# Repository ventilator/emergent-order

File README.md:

# /dev/emergent_order

An experiment in chaos and structure, presented at 39c3 (39th Chaos Communication Congress).

A 1×1×1m LED cube art installation filled with 1200 individually addressable WS2812B LEDs, creating a volumetric 3D display.

## Overview

This repository contains most materials involved in creating the LED cube installation: software, firmware, animations, 3D mechanical parts, PCB designs, calibration tools, and documentation. The aim is to document the complete structure of the cube and make relevant tools and designs available to others who want to build their own version, learn from the project, create derivative works, or apply these concepts in entirely new ways.

## Project Structure

This repository contains the following subdirectories:

**Note:** Some directories mentioned below may not yet be available in the repository. We are actively uploading the remaining materials and expect to have everything published within the next few days.

### Hardware & Electronics

- **`controller_pcb/`** - KiCad project for a high-performance 8-channel WS2812 controller based on the Raspberry Pi Pico. Features include USB streaming mode, standalone operation with built-in test patterns, SD card playback, comprehensive monitoring (voltage, current, temperature), and per-channel smart fuse protection (3.7A). Supports up to 200 LEDs per channel at 60Hz. See [controller_pcb/README.md](controller_pcb/README.md) for complete specifications.

- **`pico_firmware/`** - C firmware for the Raspberry Pi Pico that drives 8 independent WS2812B channels via PIO hardware. Features gamma correction, automatic current limiting, hardware monitoring (temperature, current, voltage), channel fault detection, and built-in test patterns including a ternary-encoded calibration pattern for camera-based position recovery. See [pico_firmware/README.md](pico_firmware/README.md) for protocol specification and development setup.

- **`mechanical/`** - 3D printable parts (base, corners, combs, controller mounts) and carbon fiber tube specifications for building the physical cube structure. See [mechanical/README.md](mechanical/README.md) for details.

### Software & Control

- **`showrunner/`** - Node.js service that plays LED animations on the cube, streaming frames at 30-60 FPS over serial to the Pico firmware. Supports hot-swappable animations and WebSocket interface for live streaming. See [showrunner/README.md](showrunner/README.md) for details.

- **`animations/`** - JavaScript animation scripts that generate LED patterns using 3D math (SDF primitives, planes, spheres, fire effects, etc.). See [animations/README.md](animations/README.md) for examples and animation format.

- **`animation_designer/`** - Web-based tool for designing and previewing animations before deploying them to the cube. See [animation_designer/README.md](animation_designer/README.md) for usage instructions.

### Calibration & Utilities

- **`calibration/`** - Tools for recovering 3D LED positions from video captures of the cube. Includes video frame extraction, LED detection with ternary color-coded identification, and multi-camera 3D triangulation with bundle adjustment. Features both Python CLI tools and a web-based detector with real-time visualization. See [calibration/README.md](calibration/README.md) for complete workflow and encoding scheme documentation.

- **`ws2serial/`** - Python utility for testing and interfacing with WS2812 LED strips over USB serial during development. Provides a WebSocket-to-serial adapter allowing the animation designer web tool to stream pixel data over the network to the Pico controller. See [ws2serial/README.md](ws2serial/README.md) for details.

- **`testdevice/`** - MicroPython code for ESP32-C3 to quickly test single LED strings during installation and teardown. See [testdevice/README.md](testdevice/README.md) for details.

### Prototypes

- **`minikube/`** - Smaller ~20×20×20cm prototype cube with MicroPython firmware and mechanical designs for ESP32-C3. See [minikube/README.md](minikube/README.md) for details.

## Technical Specifications

- **Physical size:** 1×1×1 meter cube
- **LEDs:** 1200 individually addressable WS2812B LEDs
- **Structure:** Carbon fiber tubes (20×18mm) with 3D printed corner connectors
- **Controller:** Raspberry Pi Pico-based 8-channel controller (can be driven by Raspberry Pi 3 or run standalone)
- **Power:** Custom 4-layer PCB with 8-channel power distribution, smart fuse protection (3.7A per channel), and comprehensive monitoring
- **Software:** Node.js showrunner + JavaScript animation framework (USB streaming), or standalone test patterns
- **Communication:** USB serial (Pi 3 → Pico), PIO-based WS2812B output, WebSocket interface for live animation streaming

## Development Approach

Most of the code in this project was synthesized ("vibe coded") using various Anthropic Claude models. The goal was to rapidly prototype and get something working, so the code may not be well understood in all places or may contain bugs. However, key decisions about architecture, algorithms and artistic content were provided by humans, just not manually implemented line-by-line.

## License

See the license files in individual directories or license text in source files.

In general:
- **Code/Software:** MIT License
- **3D Models:** CC-BY 4.0
- **PCB Designs:** CERN-OHL-W (CERN Open Hardware License - Weakly Reciprocal)

## Contributing

This project was created for 39c3. Feel free to fork, modify, and create your own versions. If you build something based on this work, we'd love to hear about it!

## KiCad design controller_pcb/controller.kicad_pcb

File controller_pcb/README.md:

# 8-Channel WS2812 Controller

High-performance WS2812 LED controller based on the Raspberry Pi Pico, designed for driving large LED installations with up to 8 independent channels.

## Features

- **8 independent WS2812 channels** - Drive up to 200 LEDs per channel @ 60Hz
- **Multiple operation modes:**
  - USB streaming mode (real-time control from computer)
  - Standalone mode (run animations directly on Pico)
  - SD card playback mode (hardware ready, firmware not yet implemented)
- **Built-in test patterns** for calibration and diagnostics
- **Comprehensive monitoring** - voltage, current, and temperature sensing
- **Advanced protection** - smart fuses, PTC, and TVS diodes

## Hardware Specifications

### PCB Design
- **4-layer PCB**
- **Raspberry Pi Pico** microcontroller (direct solder or via header)
- Compact form factor

### LED Output Channels
- **8 independent channels** driven via PIO state machines
- **3.3V to 5V level shifters** for reliable WS2812 communication
- **Smart fuse protection** (TPS259251) set to 3.7A per channel
- **TVS diodes** on all data lines for protection

### Power System
- **5V input** via XT60 connector
- **Input PTC** for overcurrent protection
- **5V auxiliary output** for powering additional devices (fans, Raspberry Pi, etc.)
- **INA226 current/voltage monitor** for real-time power consumption tracking

### Sensing and Monitoring
- **Input power monitoring** via INA226 (voltage and current)
- **2× NTC temperature sensors** for thermal monitoring
- **Per-channel voltage sensing** via 8:1 analog multiplexer
- **Trip detection** - automatic fault detection when channels go offline

### User Interface
- **2 buttons** for pattern selection and reset
- **2 status LEDs** (activity and fault indicators)
- **I2C OLED display header** for local status display (optional)

### Storage
- **SD card slot** for storing animations and configuration files
- **Note:** SD card support is not currently implemented in the firmware, but it was verified that the slot is correctly wired and the Pico can access data on an SD card

## Implementation & Assembly Notes

### Capacitors
- The layout contains space for through-hole capacitors on the input rail and on each output rail
- These were not fitted on the controller that ran the installation and can be considered optional

### Channel Output Connectors
- The pin headers on the channel outputs do fit into JST-SM plugs commonly used with LED strings
- However, the spacing of the pin headers is too tight for two JST-SM plugs next to each other
- There is no mechanical interlocking, and if you pass any decent current (over 1A) these connections will get quite warm, especially if not well inserted
- **Recommendation:** For the controller used in the installation, we soldered pigtails with JST-SM sockets directly to the controller PCB for more reliable connections

### Pico Mounting
- The Pi Pico was mounted with a socket to allow easier exchange in case of failure
- This is recommended over direct soldering for serviceability

## Firmware

See `../pico_firmware/` for the Raspberry Pi Pico firmware source code.

## License

Hardware design licensed under **CERN-OHL-W** (CERN Open Hardware License - Weakly Reciprocal)

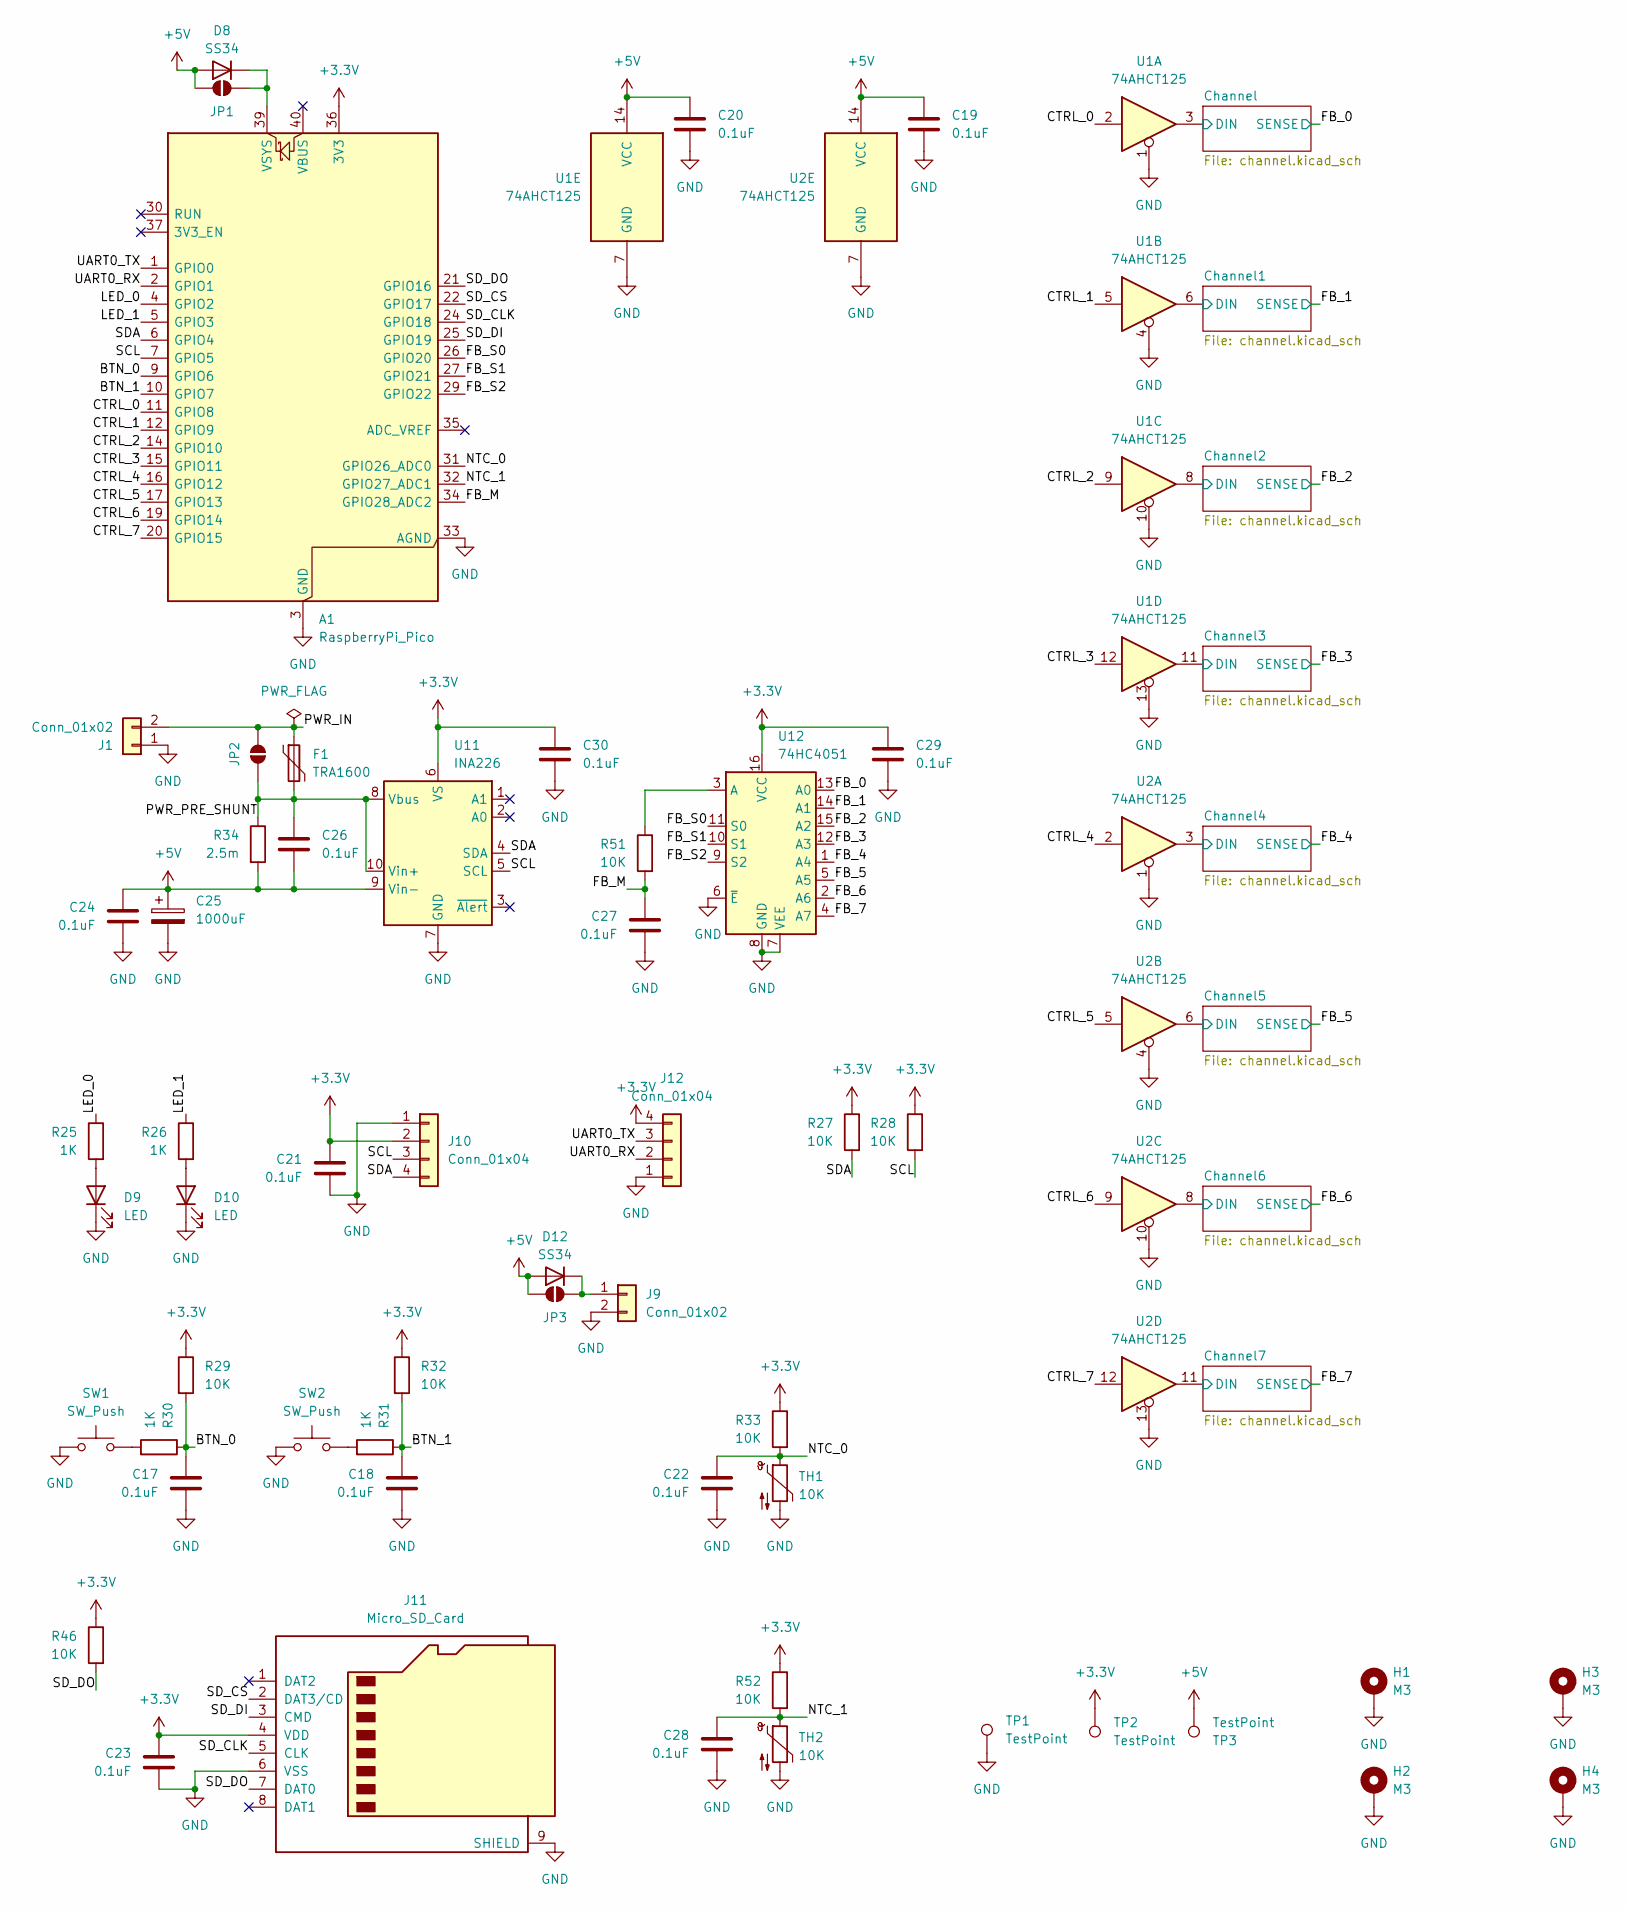
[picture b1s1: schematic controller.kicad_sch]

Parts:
A1: RaspberryPi_Pico; RaspberryPi_Pico_Common_Unspecified
C17, C18, C19, C20, C21, C22, C23, C24, C26, C27, C28, C29, C30: 0.1uF; C_0603_1608Metric
C25: 1000uF; C_Radial_D12.5mm_H20.0mm_P5.00mm; LCSC C88743
D8, D12: SS34; D_SMA; LCSC C8678
D9, D10: LED; LED_0805_2012Metric
F1: TRA1600; Fuse_Bourns_MF-RHT1300; LCSC C5678529
H1, H2, H3, H4: M3; MountingHole_3.2mm_M3_ISO7380_Pad_TopBottom
J1: Conn_01x02; AMASS_XT60PW-M_1x02_P7.20mm_Horizontal; LCSC C98732
J9: Conn_01x02; JST_PH_S2B-PH-K_1x02_P2.00mm_Horizontal
J10, J12: Conn_01x04; PinHeader_1x04_P2.54mm_Vertical
J11: Micro_SD_Card; TF-SMD_TF-021B-H265; LCSC C498185
JP1, JP2, JP3: SolderJumper_2_Open; SolderJumper-2_P1.3mm_Open_Pad1.0x1.5mm
R25, R26, R30, R31: 1K; R_0603_1608Metric
R27, R28, R29, R32, R33, R46, R51, R52: 10K; R_0603_1608Metric
R34: 2.5m; R_2512_6332Metric; LCSC C7420002
SW1, SW2: SW_Push; SW_PUSH_6mm_H5mm
TH1, TH2: 10K; R_0603_1608Metric
TP1: TestPoint; TestPoint_THTPad_2.0x2.0mm_Drill1.0mm
TP2, TP3: TestPoint; TestPoint_THTPad_D2.0mm_Drill1.0mm
U1, U2: 74AHCT125; TSSOP-14_4.4x5mm_P0.65mm; LCSC C36365
U11: INA226; VSSOP-10_3x3mm_P0.5mm; LCSC C49851
U12: 74HC4051; TSSOP-16_4.4x5mm_P0.65mm; LCSC C352826

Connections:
+3.3V: A1.36 (3V3), C21.1, C23.1, C29.1, C30.1, J10.2, J11.4 (VDD), J12.4, R27.1, R28.1, R29.1, R32.1, R33.1, R46.1, R52.1, TP2.1, U11.6 (VS), U12.16 (VCC)
+5V: C19.1, C20.1, C24.1, C25.1, C26.2, D8.2 (A), D12.2 (A), JP1.2 (B), JP3.2 (B), R34.2, TP3.1, U1.14 (VCC), U2.14 (VCC), U11.9 (Vin-); also elsewhere on the board
/BTN_0: A1.9 (GPIO6), C17.1, R29.2, R30.1
/BTN_1: A1.10 (GPIO7), C18.1, R31.1, R32.2
/CTRL_0: A1.11 (GPIO8), U1.2
/CTRL_1: A1.12 (GPIO9), U1.5
/CTRL_2: A1.14 (GPIO10), U1.9
/CTRL_3: A1.15 (GPIO11), U1.12
/CTRL_4: A1.16 (GPIO12), U2.2
/CTRL_5: A1.17 (GPIO13), U2.5
/CTRL_6: A1.19 (GPIO14), U2.9
/CTRL_7: A1.20 (GPIO15), U2.12
/Channel1/DIN: U1.6; also elsewhere on the board
/Channel2/DIN: U1.8; also elsewhere on the board
/Channel3/DIN: U1.11; also elsewhere on the board
/Channel4/DIN: U2.3; also elsewhere on the board
/Channel5/DIN: U2.6; also elsewhere on the board
/Channel6/DIN: U2.8; also elsewhere on the board
/Channel7/DIN: U2.11; also elsewhere on the board
/Channel/DIN: U1.3; also elsewhere on the board
/FB_0: U12.13 (A0); also elsewhere on the board
/FB_1: U12.14 (A1); also elsewhere on the board
/FB_2: U12.15 (A2); also elsewhere on the board
/FB_3: U12.12 (A3); also elsewhere on the board
/FB_4: U12.1 (A4); also elsewhere on the board
/FB_5: U12.5 (A5); also elsewhere on the board
/FB_6: U12.2 (A6); also elsewhere on the board
/FB_7: U12.4 (A7); also elsewhere on the board
/FB_M: A1.34 (GPIO28_ADC2), C27.1, R51.2
/FB_S0: A1.26 (GPIO20), U12.11 (S0)
/FB_S1: A1.27 (GPIO21), U12.10 (S1)
/FB_S2: A1.29 (GPIO22), U12.9 (S2)
/LED_0: A1.4 (GPIO2), R25.1
/LED_1: A1.5 (GPIO3), R26.1
/NTC_0: A1.31 (GPIO26_ADC0), C22.1, R33.2, TH1.1
/NTC_1: A1.32 (GPIO27_ADC1), C28.1, R52.2, TH2.1
/PWR_IN: F1.1, J1.2, JP2.2 (B)
/PWR_PRE_SHUNT: C26.1, F1.2, JP2.1 (A), R34.1, U11.8 (Vbus), U11.10 (Vin+)
/SCL: A1.7 (GPIO5), J10.3, R28.2, U11.5 (SCL)
/SDA: A1.6 (GPIO4), J10.4, R27.2, U11.4 (SDA)
/SD_CLK: A1.24 (GPIO18), J11.5 (CLK)
/SD_CS: A1.22 (GPIO17), J11.2 (DAT3/CD)
/SD_DI: A1.25 (GPIO19), J11.3 (CMD)
/SD_DO: A1.21 (GPIO16), J11.7 (DAT0), R46.2
/UART0_RX: A1.2 (GPIO1), J12.2
/UART0_TX: A1.1 (GPIO0), J12.3
GND: A1.3 (GND), A1.8 (GND), A1.13 (GND), A1.18 (GND), A1.23 (GND), A1.28 (GND), A1.33 (AGND), A1.38 (GND), C17.2, C18.2, C19.2, C20.2, C21.2, C22.2, C23.2, C24.2, C25.2, C27.2, C28.2, C29.2, C30.2, D9.1 (K), D10.1 (K), H1.1, H2.1, H3.1, H4.1, J1.1, J9.2, J10.1, J11.6 (VSS), J11.9 (SHIELD), J11.10 (SHIELD), J12.1, SW1.1, SW2.1, TH1.2, TH2.2, TP1.1, U1.1, U1.4, U1.7 (GND), U1.10, U1.13, U2.1, U2.4, U2.7 (GND), U2.10, U2.13, U11.7 (GND), U12.6 (~E), U12.7 (VEE), U12.8 (GND); also elsewhere on the board
unnamed: A1.39 (VSYS), D8.1 (K), JP1.1 (A)
unnamed: D9.2 (A), R25.2
unnamed: D10.2 (A), R26.2
unnamed: D12.1 (K), J9.1, JP3.1 (A)
unnamed: R30.2, SW1.2
unnamed: R31.2, SW2.2
unnamed: R51.1, U12.3 (A)

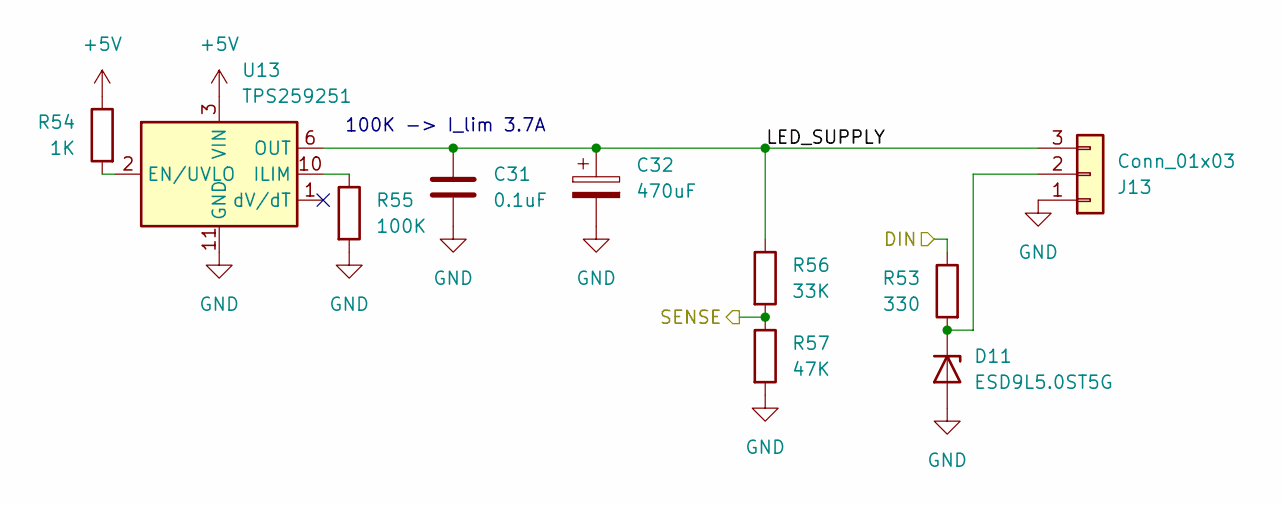
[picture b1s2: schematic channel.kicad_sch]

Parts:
C31: 0.1uF; C_0603_1608Metric
C32: 470uF; C_Radial_D10.0mm_H16.0mm_P5.00mm; LCSC C88732
D11: ESD9L5.0ST5G; D_SOD-923; LCSC C82326
J13: Conn_01x03; PinHeader_1x03_P2.54mm_Vertical
R53: 330; R_0603_1608Metric
R54: 1K; R_0603_1608Metric
R55: 100K; R_0603_1608Metric
R56: 33K; R_0603_1608Metric
R57: 47K; R_0603_1608Metric
U13: TPS259251; VSON-10-1EP_3x3mm_P0.5mm_EP1.65x2.4mm_ThermalVias; LCSC C527680

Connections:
+5V: R54.1, U13.3 (VIN), U13.4 (VIN), U13.5 (VIN); also elsewhere on the board
/Channel/DIN: R53.1; also elsewhere on the board
/Channel/LED_SUPPLY: C31.1, C32.1, J13.3, R56.1, U13.6 (OUT), U13.7 (OUT), U13.8 (OUT)
/FB_0: R56.2, R57.1; also elsewhere on the board
GND: C31.2, C32.2, D11.2 (A), J13.1, R55.2, R57.2, U13.11 (GND); also elsewhere on the board
unnamed: D11.1 (K), J13.2, R53.2
unnamed: R54.2, U13.2 (EN/UVLO)
unnamed: R55.1, U13.10 (ILIM)

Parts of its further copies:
C1, C3, C5, C7, C9, C11, C13: 0.1uF; C_0603_1608Metric
C2, C4, C6, C8, C10, C12, C14: 470uF; C_Radial_D10.0mm_H16.0mm_P5.00mm; LCSC C88732
D1, D2, D3, D4, D5, D6, D7: ESD9L5.0ST5G; D_SOD-923; LCSC C82326
J2, J3, J4, J5, J6, J7, J8: Conn_01x03; PinHeader_1x03_P2.54mm_Vertical
R1, R6, R11, R16, R21, R36, R41: 1K; R_0603_1608Metric
R2, R7, R12, R17, R22, R37, R42: 100K; R_0603_1608Metric
R3, R8, R13, R18, R23, R38, R43: 33K; R_0603_1608Metric
R4, R9, R14, R19, R24, R39, R44: 47K; R_0603_1608Metric
R5, R10, R15, R20, R35, R40, R45: 330; R_0603_1608Metric
U3, U4, U5, U6, U7, U8, U9: TPS259251; VSON-10-1EP_3x3mm_P0.5mm_EP1.65x2.4mm_ThermalVias; LCSC C527680

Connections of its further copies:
+5V: R1.1, R6.1, R11.1, R16.1, R21.1, R36.1, R41.1, U3.3 (VIN), U3.4 (VIN), U3.5 (VIN), U4.3 (VIN), U4.4 (VIN), U4.5 (VIN), U5.3 (VIN), U5.4 (VIN), U5.5 (VIN), U6.3 (VIN), U6.4 (VIN), U6.5 (VIN), U7.3 (VIN), U7.4 (VIN), U7.5 (VIN), U8.3 (VIN), U8.4 (VIN), U8.5 (VIN), U9.3 (VIN), U9.4 (VIN), U9.5 (VIN); also elsewhere on the board
/Channel1/DIN: R5.1; also elsewhere on the board
/Channel1/LED_SUPPLY: C1.1, C2.1, J2.3, R3.1, U3.6 (OUT), U3.7 (OUT), U3.8 (OUT)
/Channel2/DIN: R10.1; also elsewhere on the board
/Channel2/LED_SUPPLY: C3.1, C4.1, J3.3, R8.1, U4.6 (OUT), U4.7 (OUT), U4.8 (OUT)
/Channel3/DIN: R15.1; also elsewhere on the board
/Channel3/LED_SUPPLY: C5.1, C6.1, J4.3, R13.1, U5.6 (OUT), U5.7 (OUT), U5.8 (OUT)
/Channel4/DIN: R20.1; also elsewhere on the board
/Channel4/LED_SUPPLY: C7.1, C8.1, J5.3, R18.1, U6.6 (OUT), U6.7 (OUT), U6.8 (OUT)
/Channel5/DIN: R35.1; also elsewhere on the board
/Channel5/LED_SUPPLY: C9.1, C10.1, J6.3, R23.1, U7.6 (OUT), U7.7 (OUT), U7.8 (OUT)
/Channel6/DIN: R40.1; also elsewhere on the board
/Channel6/LED_SUPPLY: C11.1, C12.1, J7.3, R38.1, U8.6 (OUT), U8.7 (OUT), U8.8 (OUT)
/Channel7/DIN: R45.1; also elsewhere on the board
/Channel7/LED_SUPPLY: C13.1, C14.1, J8.3, R43.1, U9.6 (OUT), U9.7 (OUT), U9.8 (OUT)
/FB_1: R3.2, R4.1; also elsewhere on the board
/FB_2: R8.2, R9.1; also elsewhere on the board
/FB_3: R13.2, R14.1; also elsewhere on the board
/FB_4: R18.2, R19.1; also elsewhere on the board
/FB_5: R23.2, R24.1; also elsewhere on the board
/FB_6: R38.2, R39.1; also elsewhere on the board
/FB_7: R43.2, R44.1; also elsewhere on the board
GND: C1.2, C2.2, C3.2, C4.2, C5.2, C6.2, C7.2, C8.2, C9.2, C10.2, C11.2, C12.2, C13.2, C14.2, D1.2 (A), D2.2 (A), D3.2 (A), D4.2 (A), D5.2 (A), D6.2 (A), D7.2 (A), J2.1, J3.1, J4.1, J5.1, J6.1, J7.1, J8.1, R2.2, R4.2, R7.2, R9.2, R12.2, R14.2, R17.2, R19.2, R22.2, R24.2, R37.2, R39.2, R42.2, R44.2, U3.11 (GND), U4.11 (GND), U5.11 (GND), U6.11 (GND), U7.11 (GND), U8.11 (GND), U9.11 (GND); also elsewhere on the board
unnamed: D1.1 (K), J2.2, R5.2
unnamed: D2.1 (K), J3.2, R10.2
unnamed: D3.1 (K), J4.2, R15.2
unnamed: D4.1 (K), J5.2, R20.2
unnamed: D5.1 (K), J6.2, R35.2
unnamed: D6.1 (K), J7.2, R40.2
unnamed: D7.1 (K), J8.2, R45.2
unnamed: R1.2, U3.2 (EN/UVLO)
unnamed: R2.1, U3.10 (ILIM)
unnamed: R6.2, U4.2 (EN/UVLO)
unnamed: R7.1, U4.10 (ILIM)
unnamed: R11.2, U5.2 (EN/UVLO)
unnamed: R12.1, U5.10 (ILIM)
unnamed: R16.2, U6.2 (EN/UVLO)
unnamed: R17.1, U6.10 (ILIM)
unnamed: R21.2, U7.2 (EN/UVLO)
unnamed: R22.1, U7.10 (ILIM)
unnamed: R36.2, U8.2 (EN/UVLO)
unnamed: R37.1, U8.10 (ILIM)
unnamed: R41.2, U9.2 (EN/UVLO)
unnamed: R42.1, U9.10 (ILIM)

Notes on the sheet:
100K -> I_lim 3.7A

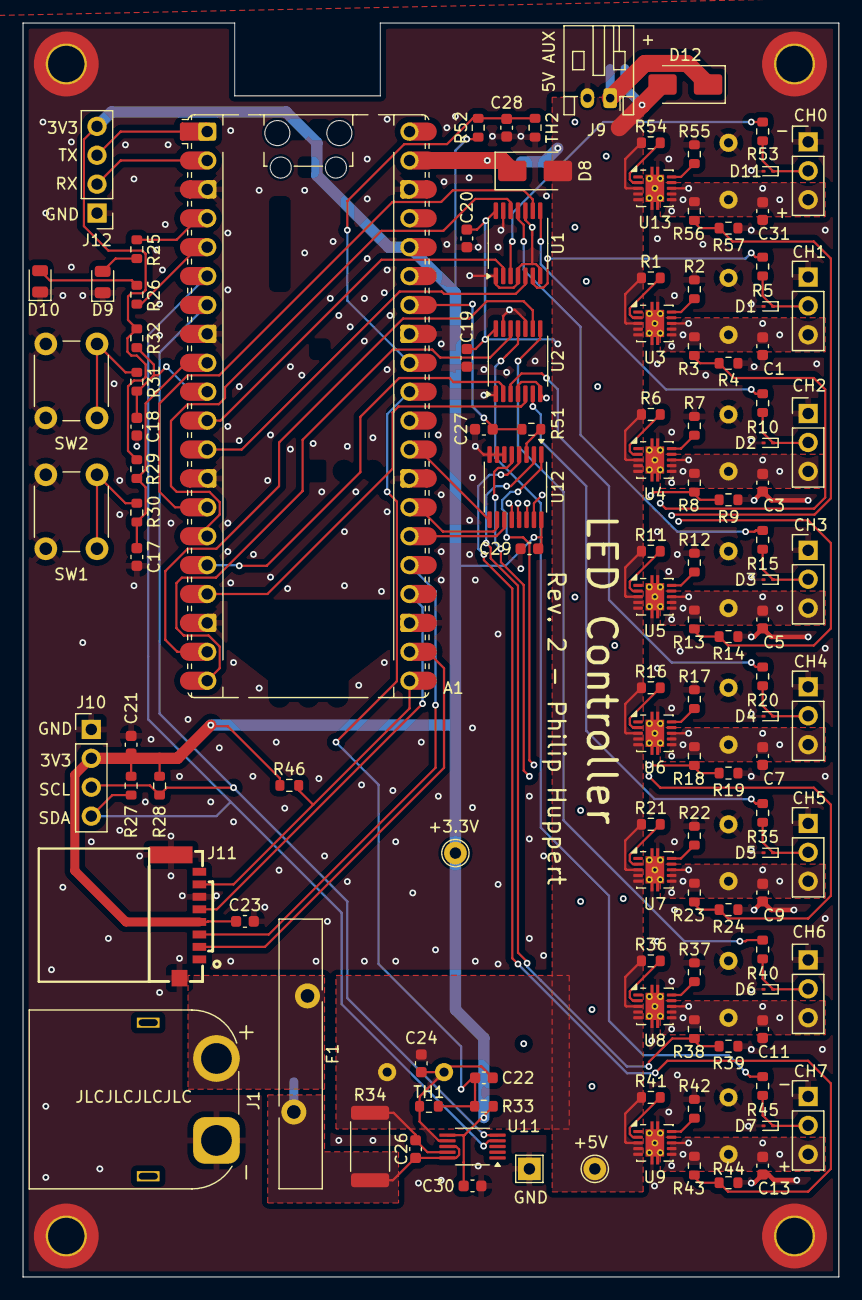
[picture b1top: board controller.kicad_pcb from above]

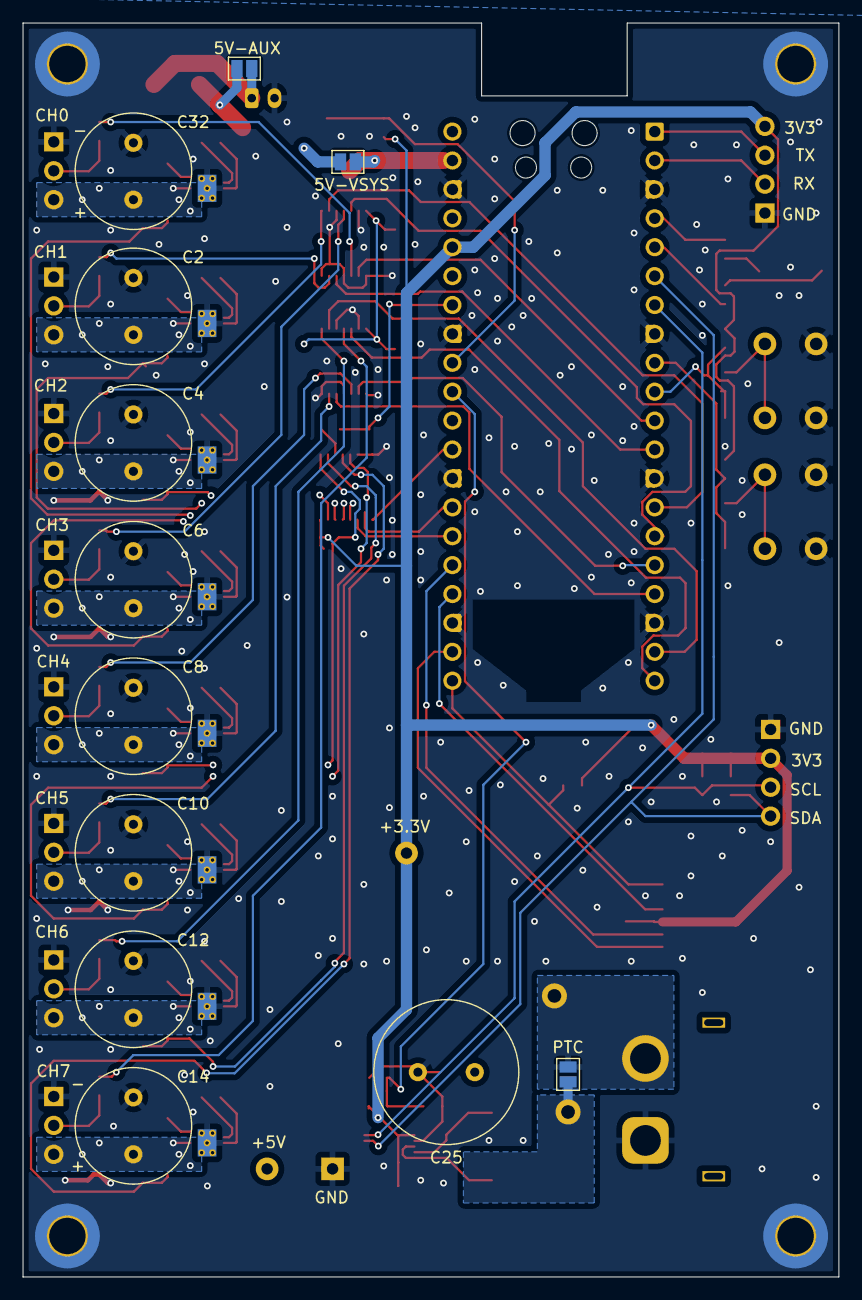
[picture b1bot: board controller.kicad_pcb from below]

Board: 4 copper layers, 71.7 x 110.2 mm, 136 parts (12 on the bottom side), 86 nets.

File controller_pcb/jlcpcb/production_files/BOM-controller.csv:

Comment,Designator,Footprint,LCSC,Quantity
1000uF,C25,C_Radial_D12.5mm_H20.0mm_P5.00mm,C88743,1
2.5m,R34,R_2512_6332Metric,C7420002,1
470uF,"C10,C12,C14,C2,C32,C4,C6,C8",C_Radial_D10.0mm_H16.0mm_P5.00mm,C88732,8
74AHCT125,"U1,U2",TSSOP-14_4.4x5mm_P0.65mm,C36365,2
74HC4051,U12,TSSOP-16_4.4x5mm_P0.65mm,C352826,1
Conn_01x02,J1,AMASS_XT60PW-M_1x02_P7.20mm_Horizontal,C98732,1
ESD9L5.0ST5G,"D1,D11,D2,D3,D4,D5,D6,D7",D_SOD-923,C82326,8
INA226,U11,VSSOP-10_3x3mm_P0.5mm,C49851,1
Micro_SD_Card,J11,TF-SMD_TF-021B-H265,C498185,1
SS34,"D12,D8",D_SMA,C8678,2
TPS259251,"U13,U3,U4,U5,U6,U7,U8,U9",VSON-10-1EP_3x3mm_P0.5mm_EP1.65x2.4mm_ThermalVias,C527680,8
TRA1600,F1,Fuse_Bourns_MF-RHT1300,C5678529,1
10K,R32,R_0603_1608Metric,,1
10K,R29,R_0603_1608Metric,,1
1K,R6,R_0603_1608Metric,,1
47K,R44,R_0603_1608Metric,,1
0.1uF,C19,C_0603_1608Metric,,1
47K,R39,R_0603_1608Metric,,1
0.1uF,C31,C_0603_1608Metric,,1
47K,R19,R_0603_1608Metric,,1
100K,R37,R_0603_1608Metric,,1
0.1uF,C7,C_0603_1608Metric,,1
330,R10,R_0603_1608Metric,,1
1K,R26,R_0603_1608Metric,,1
33K,R3,R_0603_1608Metric,,1
1K,R54,R_0603_1608Metric,,1
1K,R11,R_0603_1608Metric,,1
1K,R30,R_0603_1608Metric,,1
0.1uF,C27,C_0603_1608Metric,,1
0.1uF,C13,C_0603_1608Metric,,1
330,R35,R_0603_1608Metric,,1
100K,R12,R_0603_1608Metric,,1
33K,R38,R_0603_1608Metric,,1
33K,R18,R_0603_1608Metric,,1
0.1uF,C26,C_0603_1608Metric,,1
10K,R28,R_0603_1608Metric,,1
1K,R25,R_0603_1608Metric,,1
0.1uF,C5,C_0603_1608Metric,,1
1K,R41,R_0603_1608Metric,,1
330,R40,R_0603_1608Metric,,1
100K,R42,R_0603_1608Metric,,1
0.1uF,C9,C_0603_1608Metric,,1
1K,R21,R_0603_1608Metric,,1
33K,R43,R_0603_1608Metric,,1
33K,R23,R_0603_1608Metric,,1
330,R53,R_0603_1608Metric,,1
100K,R17,R_0603_1608Metric,,1
0.1uF,C24,C_0603_1608Metric,,1
10K,R52,R_0603_1608Metric,,1
47K,R9,R_0603_1608Metric,,1
0.1uF,C22,C_0603_1608Metric,,1
0.1uF,C28,C_0603_1608Metric,,1
1K,R16,R_0603_1608Metric,,1
100K,R2,R_0603_1608Metric,,1
TestPoint,TP1,TestPoint_THTPad_2.0x2.0mm_Drill1.0mm,,1
TestPoint,TP3,TestPoint_THTPad_D2.0mm_Drill1.0mm,,1
10K,TH1,R_0603_1608Metric,,1
330,R5,R_0603_1608Metric,,1
100K,R7,R_0603_1608Metric,,1
100K,R55,R_0603_1608Metric,,1
10K,R51,R_0603_1608Metric,,1
33K,R56,R_0603_1608Metric,,1
330,R45,R_0603_1608Metric,,1
10K,R33,R_0603_1608Metric,,1
47K,R24,R_0603_1608Metric,,1
0.1uF,C29,C_0603_1608Metric,,1
10K,R27,R_0603_1608Metric,,1
10K,TH2,R_0603_1608Metric,,1
1K,R36,R_0603_1608Metric,,1
0.1uF,C21,C_0603_1608Metric,,1
1K,R31,R_0603_1608Metric,,1
0.1uF,C1,C_0603_1608Metric,,1
1K,R1,R_0603_1608Metric,,1
0.1uF,C3,C_0603_1608Metric,,1
0.1uF,C30,C_0603_1608Metric,,1
47K,R14,R_0603_1608Metric,,1
0.1uF,C23,C_0603_1608Metric,,1
0.1uF,C11,C_0603_1608Metric,,1
0.1uF,C18,C_0603_1608Metric,,1
330,R20,R_0603_1608Metric,,1
0.1uF,C17,C_0603_1608Metric,,1
47K,R57,R_0603_1608Metric,,1
TestPoint,TP2,TestPoint_THTPad_D2.0mm_Drill1.0mm,,1
33K,R8,R_0603_1608Metric,,1
33K,R13,R_0603_1608Metric,,1
100K,R22,R_0603_1608Metric,,1
0.1uF,C20,C_0603_1608Metric,,1
330,R15,R_0603_1608Metric,,1
47K,R4,R_0603_1608Metric,,1
Conn_01x02,J9,JST_PH_S2B-PH-K_1x02_P2.00mm_Horizontal,,1
10K,R46,R_0603_1608Metric,,1

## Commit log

2026-01-01 Add top-level README
2026-01-01 Add mechanical files and documentation
2026-01-01 Update top-level README
2026-01-01 Initial import of calibration utils
2026-01-03 Add calibration pattern to minikube firmware
2026-01-03 Import PCB design
2026-01-04 Add notes about controller
2026-01-17 configuration for EPS32 with 100LEDs
2026-01-17 adding debugging info to readme
2026-01-17 utf bugfix and custom calibration settings
    utf bugfix and custom calibration settings
